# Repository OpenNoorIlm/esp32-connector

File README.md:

# esp32-connector
Get fabrication ready esp32 conector for NoorRobot if you dont want wire mess up

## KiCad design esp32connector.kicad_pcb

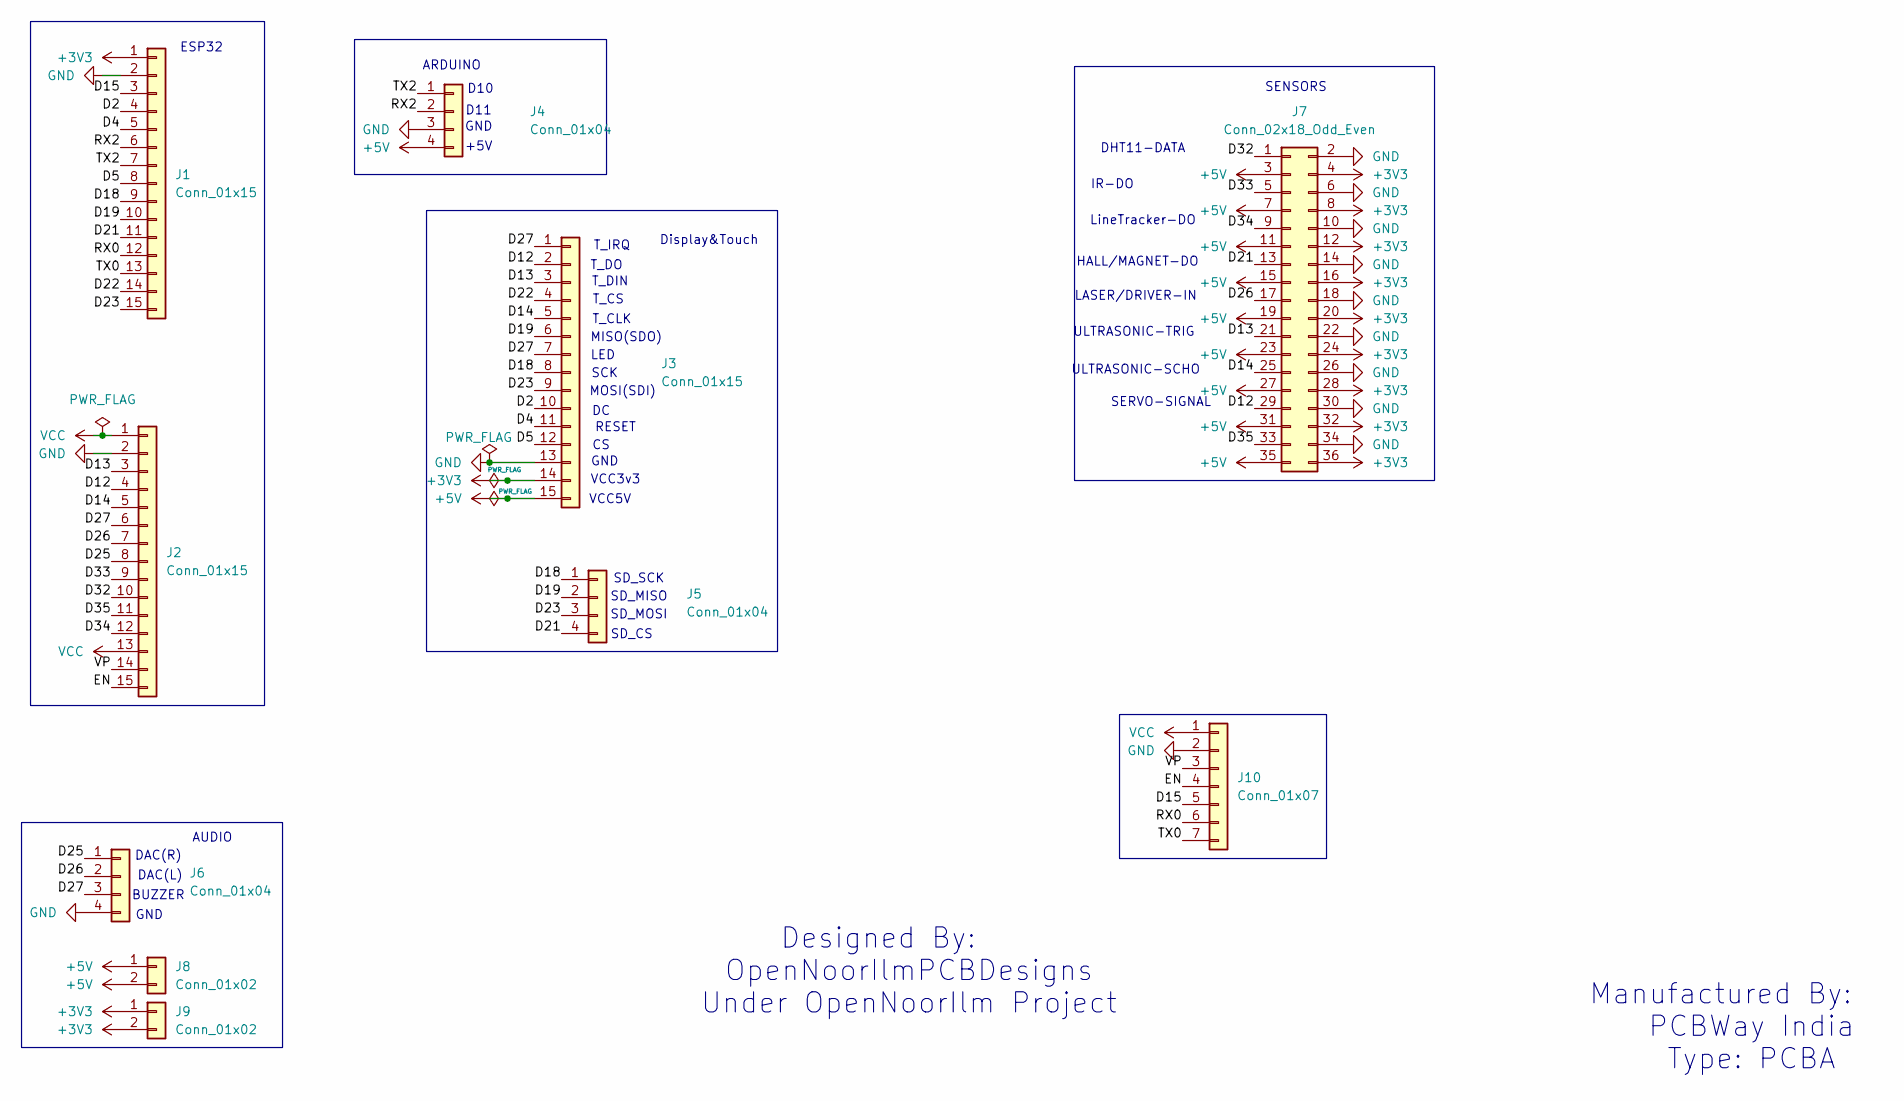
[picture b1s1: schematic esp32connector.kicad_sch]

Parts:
J1, J2, J3: Conn_01x15; PinSocket_1x15_P2.54mm_Vertical
J4, J5: Conn_01x04; PinSocket_1x04_P2.54mm_Vertical
J6: Conn_01x04; PinHeader_1x04_P2.54mm_Vertical
J7: Conn_02x18_Odd_Even; PinHeader_2x18_P2.54mm_Vertical
J8, J9: Conn_01x02; PinHeader_1x02_P2.54mm_Vertical
J10: Conn_01x07; PinHeader_1x07_P2.54mm_Vertical

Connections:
+3V3: J1.1, J3.14, J7.4, J7.8, J7.12, J7.16, J7.20, J7.24, J7.28, J7.32, J7.36, J9.1, J9.2
+5V: J3.15, J4.4, J7.3, J7.7, J7.11, J7.15, J7.19, J7.23, J7.27, J7.31, J7.35, J8.1, J8.2
/D2: J1.4, J3.10
/D4: J1.5, J3.11
/D5: J1.8, J3.12
/D12: J2.4, J3.2, J7.29
/D13: J2.3, J3.3, J7.21
/D14: J2.5, J3.5, J7.25
/D15: J1.3, J10.5
/D18: J1.9, J3.8, J5.1
/D19: J1.10, J3.6, J5.2
/D21: J1.11, J5.4, J7.13
/D22: J1.14, J3.4
/D23: J1.15, J3.9, J5.3
/D25: J2.8, J6.1
/D26: J2.7, J6.2, J7.17
/D27: J2.6, J3.1, J3.7, J6.3
/D32: J2.10, J7.1
/D33: J2.9, J7.5
/D34: J2.12, J7.9
/D35: J2.11, J7.33
/EN: J2.15, J10.4
/RX0: J1.12, J10.6
/RX2: J1.6, J4.2
/TX0: J1.13, J10.7
/TX2: J1.7, J4.1
/VP: J2.14, J10.3
GND: J1.2, J2.2, J3.13, J4.3, J6.4, J7.2, J7.6, J7.10, J7.14, J7.18, J7.22, J7.26, J7.30, J7.34, J10.2
VCC: J2.1, J2.13, J10.1

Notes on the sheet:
LED
GND
ULTRASONIC-SCHO
SD_MOSI
VCC3v3
Designed By: OpenNoorIlmPCBDesigns Under OpenNoorIlm Project
ARDUINO
SD_CS
HALL/MAGNET-DO
IR-DO
T_CS
SENSORS
T_CLK
LineTracker-DO
RESET
MISO(SDO)
MOSI(SDI)
T_DIN
LASER/DRIVER-IN
ESP32
ULTRASONIC-TRIG
DHT11-DATA
D10
T_IRQ
SERVO-SIGNAL
BUZZER
DAC(R)
SD_SCK
VCC5V
SD_MISO
T_DO
+5V
DAC(L)
D11
AUDIO
SCK
Manufactured By: PCBWay India Type: PCBA
Display&Touch

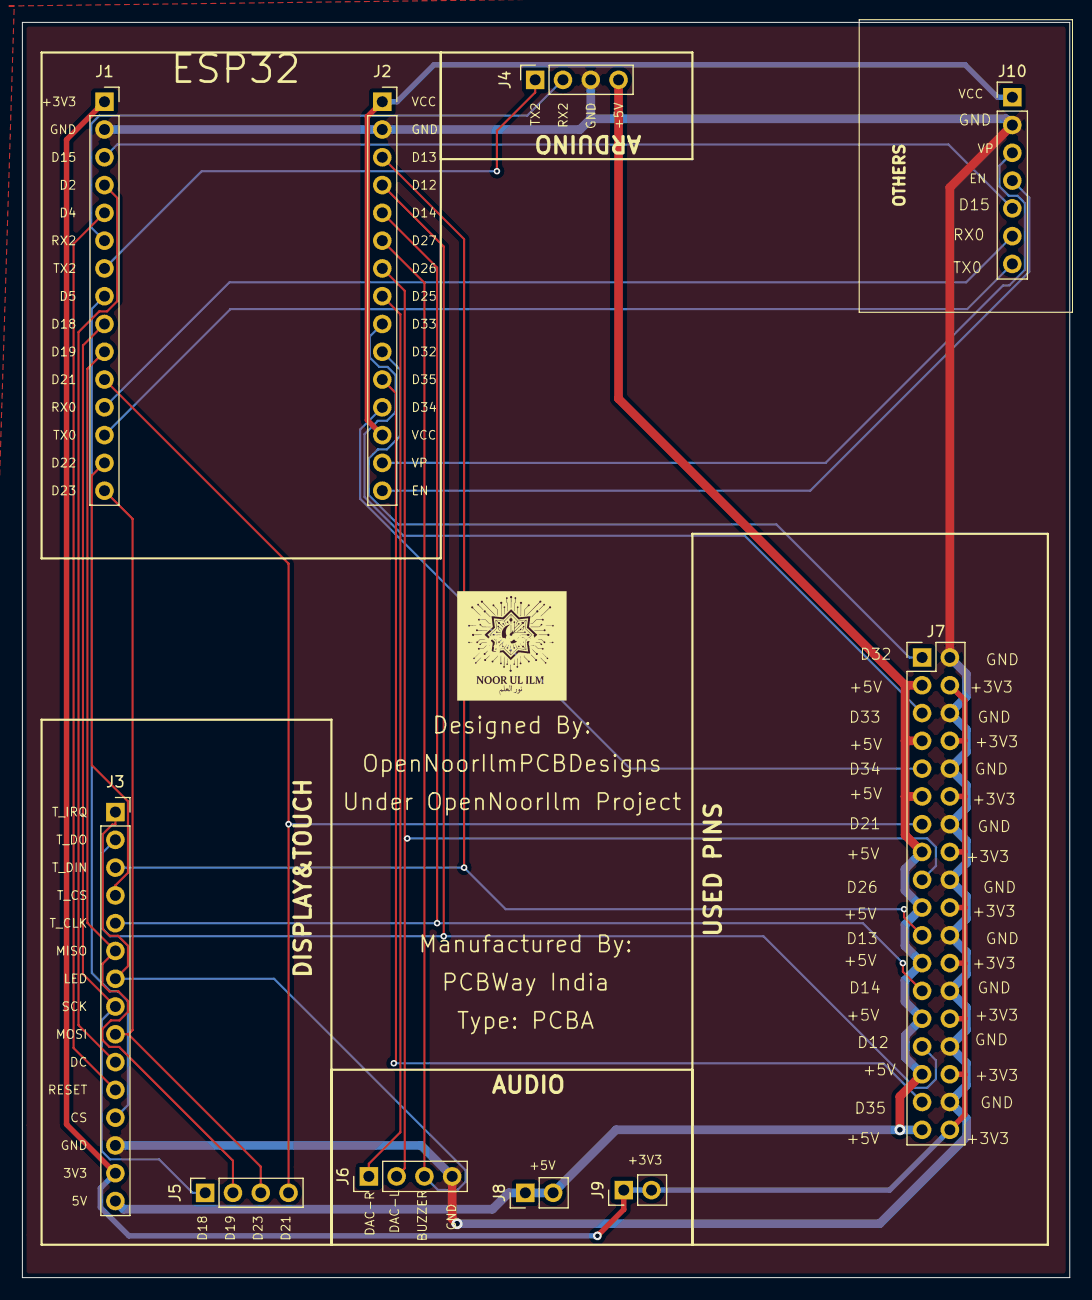
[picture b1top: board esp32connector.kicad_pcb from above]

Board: 2 copper layers, 95.8 x 114.8 mm, 10 parts (0 on the bottom side), 29 nets.
